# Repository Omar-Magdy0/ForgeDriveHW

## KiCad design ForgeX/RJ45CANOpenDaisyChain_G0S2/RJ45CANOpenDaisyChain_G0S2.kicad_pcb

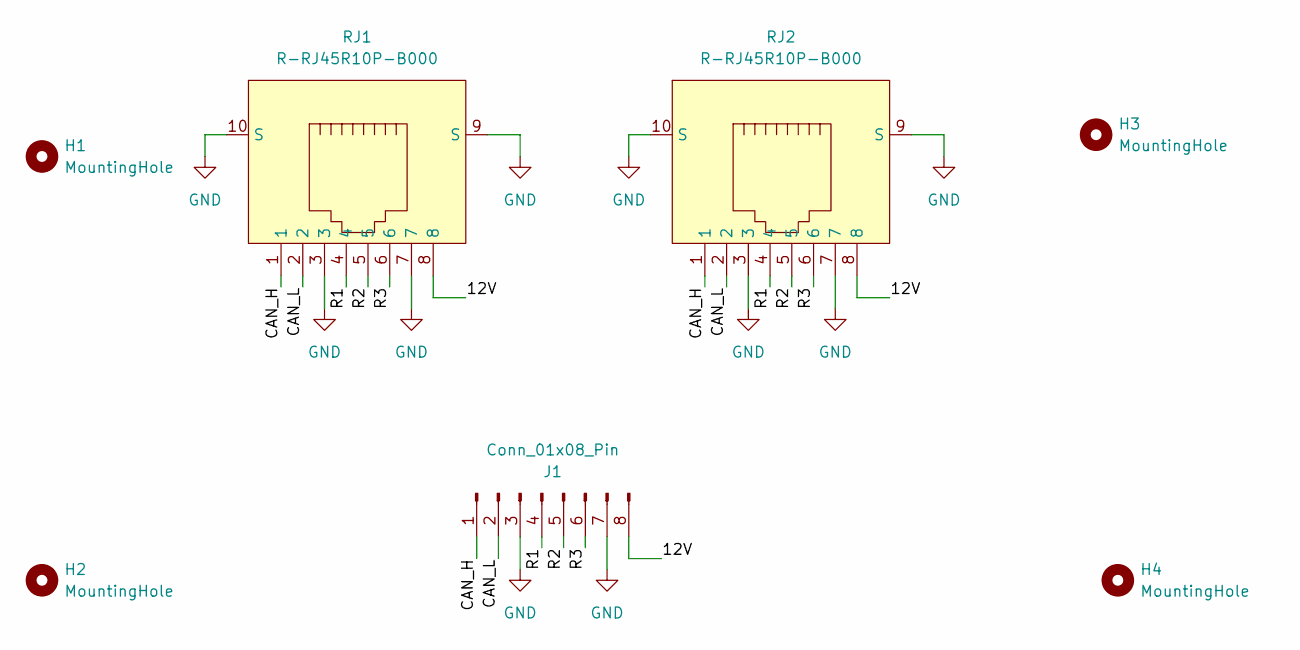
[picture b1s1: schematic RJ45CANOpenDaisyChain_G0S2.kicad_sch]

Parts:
H1, H2, H3, H4: MountingHole; MountingHole_3.2mm_M3_DIN965_Pad_TopBottom
J1: Conn_01x08_Pin; P2.54_WirePad_Header
RJ1, RJ2: R-RJ45R10P-B000; RJ45-TH_R-RJ45R10P-B000; MPN R-RJ45R10P-B000; LCSC Part C386758

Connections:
/12V: J1.8, RJ1.8, RJ2.8
/CAN_H: J1.1, RJ1.1, RJ2.1
/CAN_L: J1.2, RJ1.2, RJ2.2
/R1: J1.4, RJ1.4, RJ2.4
/R2: J1.5, RJ1.5, RJ2.5
/R3: J1.6, RJ1.6, RJ2.6
GND: J1.3, J1.7, RJ1.3, RJ1.7, RJ1.9 (S), RJ1.10 (S), RJ2.3, RJ2.7, RJ2.9 (S), RJ2.10 (S)

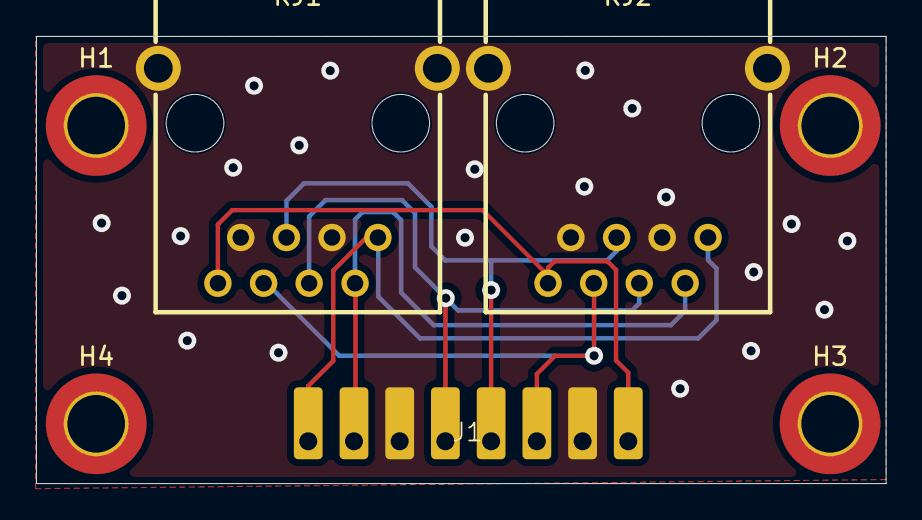
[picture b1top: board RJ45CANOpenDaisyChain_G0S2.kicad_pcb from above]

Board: 2 copper layers, 47.2 x 24.8 mm, 7 parts (0 on the bottom side), 7 nets.

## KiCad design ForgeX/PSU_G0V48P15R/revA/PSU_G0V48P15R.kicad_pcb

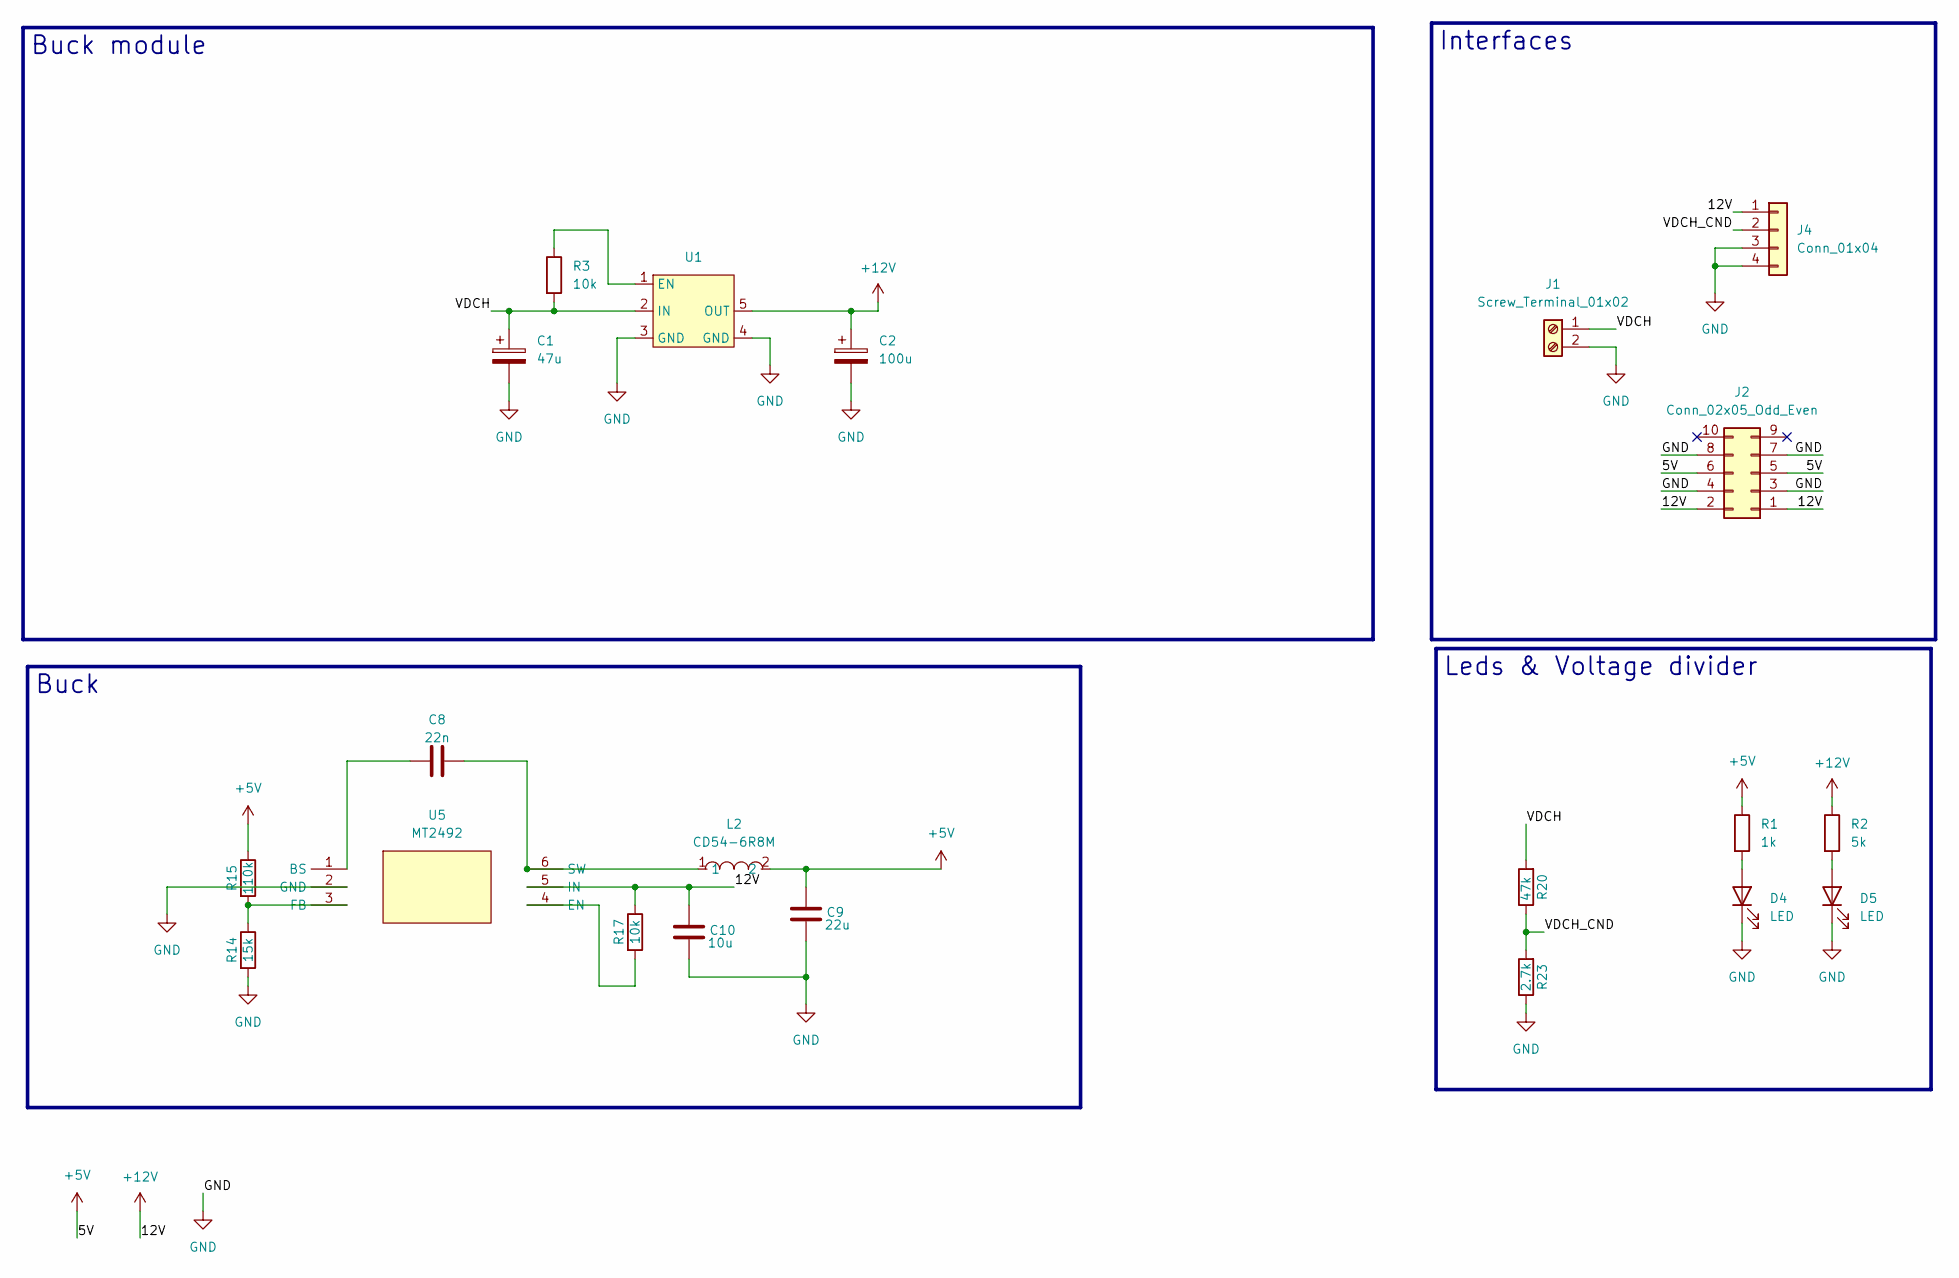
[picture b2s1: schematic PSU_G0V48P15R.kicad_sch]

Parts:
C1: 47u; CP_Radial_D10.0mm_P3.50mm
C2: 100u; CP_Radial_D10.0mm_P3.50mm
C8: 22n; C_0603_1608Metric_Pad1.08x0.95mm_HandSolder
C9: 22u; C_1206_3216Metric_Pad1.33x1.80mm_HandSolder
C10: 10u; C_1206_3216Metric_Pad1.33x1.80mm_HandSolder
D4, D5: LED; LED_1206_3216Metric_Pad1.42x1.75mm_HandSolder
J1: Screw_Terminal_01x02; SPACER_M3_PCONN_PSU
J2: Conn_02x05_Odd_Even; PinHeader_2x05_P2.54mm_Vertical
J4: Conn_01x04; JST_XH_B4B-XH-A_1x04_P2.50mm_Vertical
L2: CD54-6R8M; IND-SMD_L5.8-W5.2_CD54; MPN CD54-6R8M; LCSC Part C7588992
R1: 1k; R_1206_3216Metric_Pad1.30x1.75mm_HandSolder
R2: 5k; R_1206_3216Metric_Pad1.30x1.75mm_HandSolder
R3: 10k; R_1206_3216Metric_Pad1.30x1.75mm_HandSolder
R14: 15k; R_0603_1608Metric_Pad0.98x0.95mm_HandSolder
R15: 110k; R_0603_1608Metric_Pad0.98x0.95mm_HandSolder
R17: 10k; R_0603_1608Metric_Pad0.98x0.95mm_HandSolder
R20: 47k; R_1206_3216Metric_Pad1.30x1.75mm_HandSolder
R23: 2.7k; R_1206_3216Metric_Pad1.30x1.75mm_HandSolder
U1: HW-788abcd
U5: MT2492; SOT-23-6_L2.9-W1.6-P0.95-LS2.8-BL_3; MPN MT2492; LCSC Part C89358

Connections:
+5V: C9.1, J2.5, J2.6, L2.2, R1.1, R15.1
+12V: C2.1, C10.1, J2.1, J2.2, J4.1, R2.1, R17.1, U1.5 (OUT), U5.5 (IN)
/VDCH: C1.1, J1.1, R3.2, R20.2, U1.2 (IN)
/VDCH_CND: J4.2, R20.1, R23.2
GND: C1.2, C2.2, C9.2, C10.2, D4.1 (K), D5.1 (K), J1.2, J2.3, J2.4, J2.7, J2.8, J4.3, J4.4, R14.2, R23.1, U1.3 (GND), U1.4 (GND), U5.2 (GND)
unnamed: D4.2 (A), R1.2
unnamed: D5.2 (A), R2.2
unnamed: R3.1, U1.1 (EN)
unnamed: C8.2, U5.1 (BS)
unnamed: R17.2, U5.4 (EN)
unnamed: R14.1, R15.2, U5.3 (FB)
unnamed: C8.1, L2.1, U5.6 (SW)

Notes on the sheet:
Buck module
Buck
Interfaces
Leds & Voltage divider

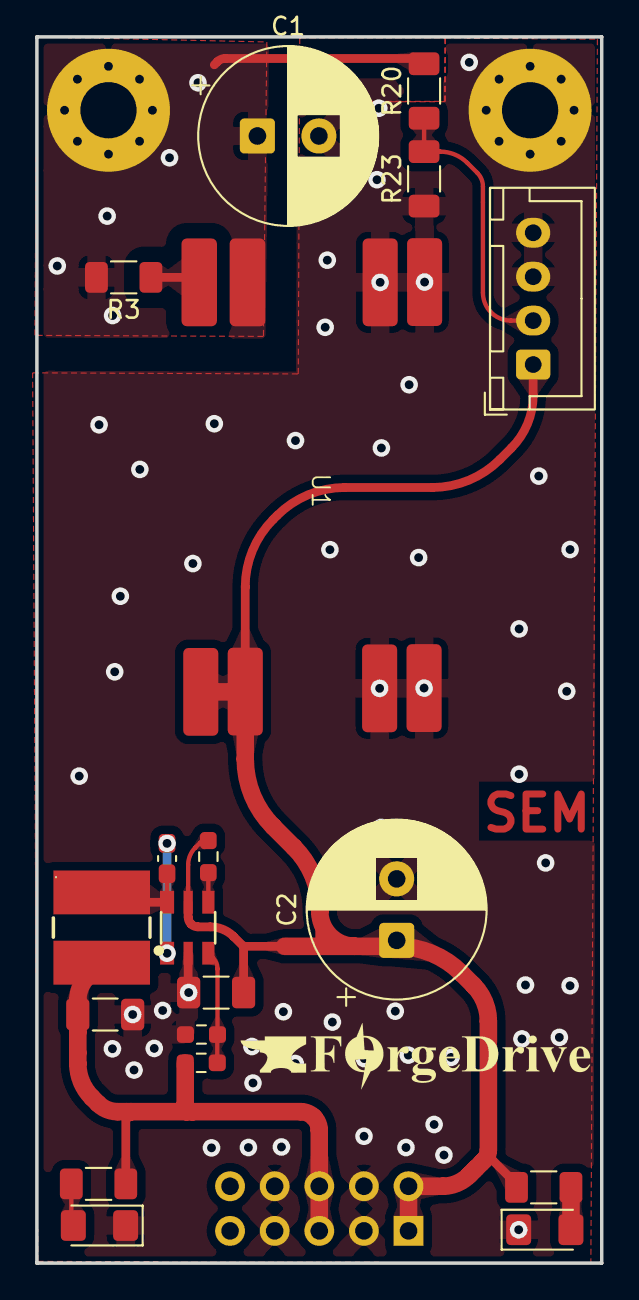
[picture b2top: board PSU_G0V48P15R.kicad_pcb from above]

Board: 2 copper layers, 32.1 x 69.8 mm, 21 parts (1 on the bottom side), 12 nets.

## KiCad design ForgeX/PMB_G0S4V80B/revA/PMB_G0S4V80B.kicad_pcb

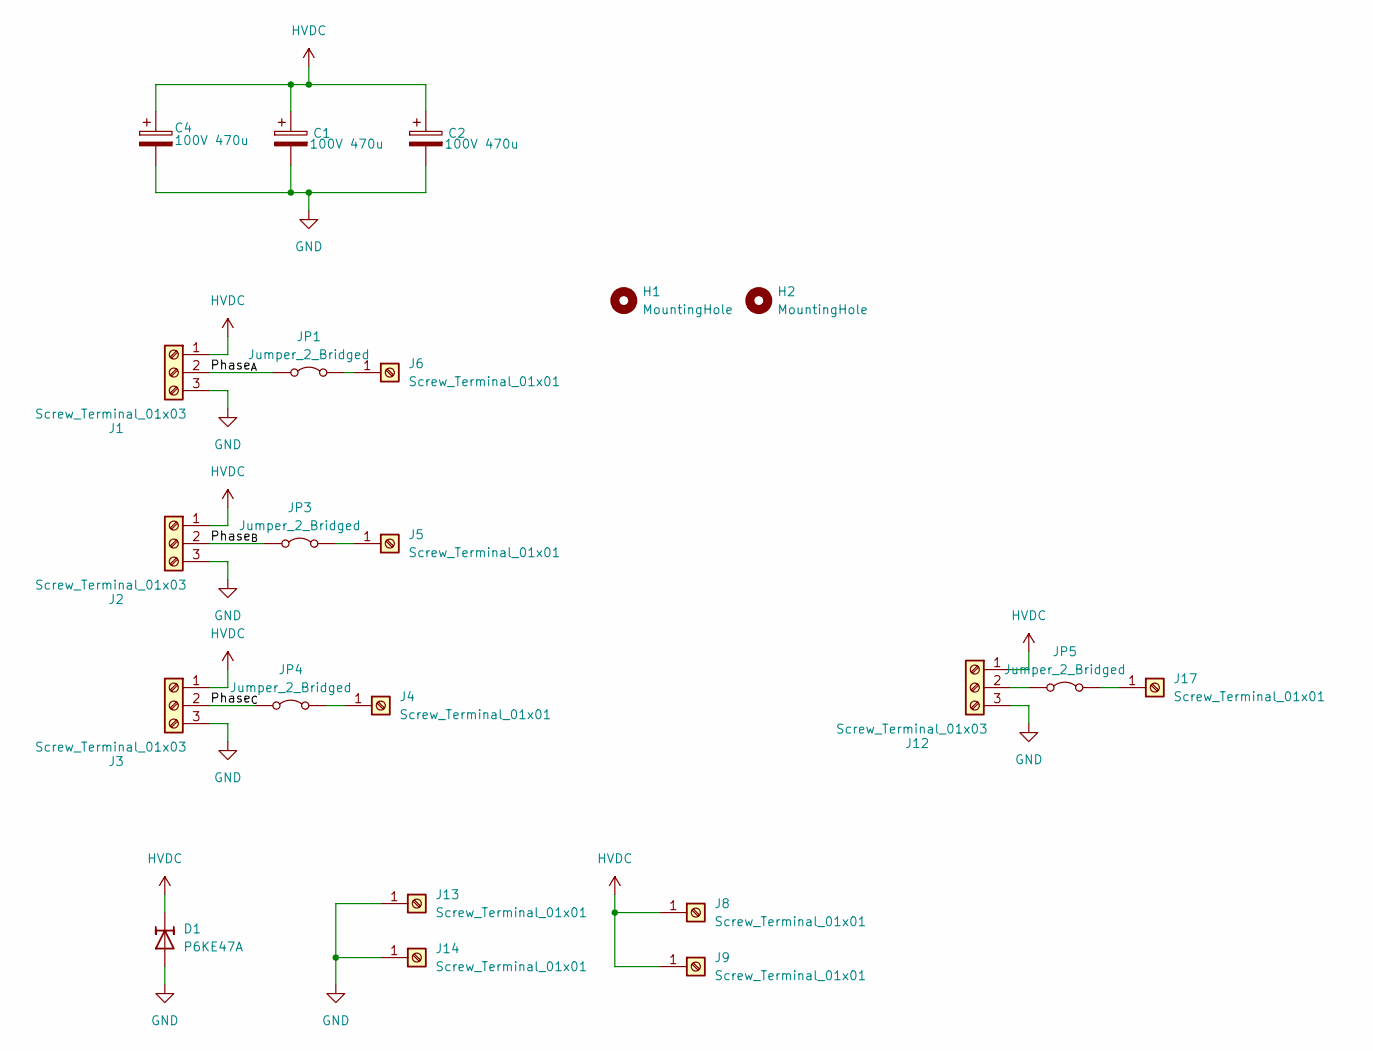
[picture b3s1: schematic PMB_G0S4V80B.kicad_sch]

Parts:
C1, C2, C4: 100V 470u; CP_Radial_D18.0mm_P7.50mm
D1: P6KE47A; D_DO-15_P10.16mm_Horizontal
H1, H2: MountingHole; MountingHole_5.3mm_M5_DIN965
J1, J2, J3, J12: Screw_Terminal_01x03; SPACER_M3_PCONN_2x03
J4, J5, J6, J8, J9, J13, J14, J17: Screw_Terminal_01x01; M3_PCONN_1x01
JP1, JP3, JP4, JP5: Jumper_2_Bridged; PowerJumper_PMB

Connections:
/Phase_{A}: J1.2, JP1.1 (A)
/Phase_{B}: J2.2, JP3.1 (A)
/Phase_{C}: J3.2, JP4.1 (A)
GND: C1.2, C2.2, C4.2, D1.2 (A), J1.3, J2.3, J3.3, J12.3, J13.1 (Pin_1_1), J14.1 (Pin_1_1)
HVDC: C1.1, C2.1, C4.1, D1.1 (K), J1.1, J2.1, J3.1, J8.1 (Pin_1_1), J9.1 (Pin_1_1), J12.1
unnamed: J4.1 (Pin_1_1), JP4.2 (B)
unnamed: J5.1 (Pin_1_1), JP3.2 (B)
unnamed: J6.1 (Pin_1_1), JP1.2 (B)
unnamed: J12.2, JP5.1 (A)
unnamed: J17.1 (Pin_1_1), JP5.2 (B)

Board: 2 copper layers, 22 parts (0 on the bottom side), 10 nets, no tracks yet.

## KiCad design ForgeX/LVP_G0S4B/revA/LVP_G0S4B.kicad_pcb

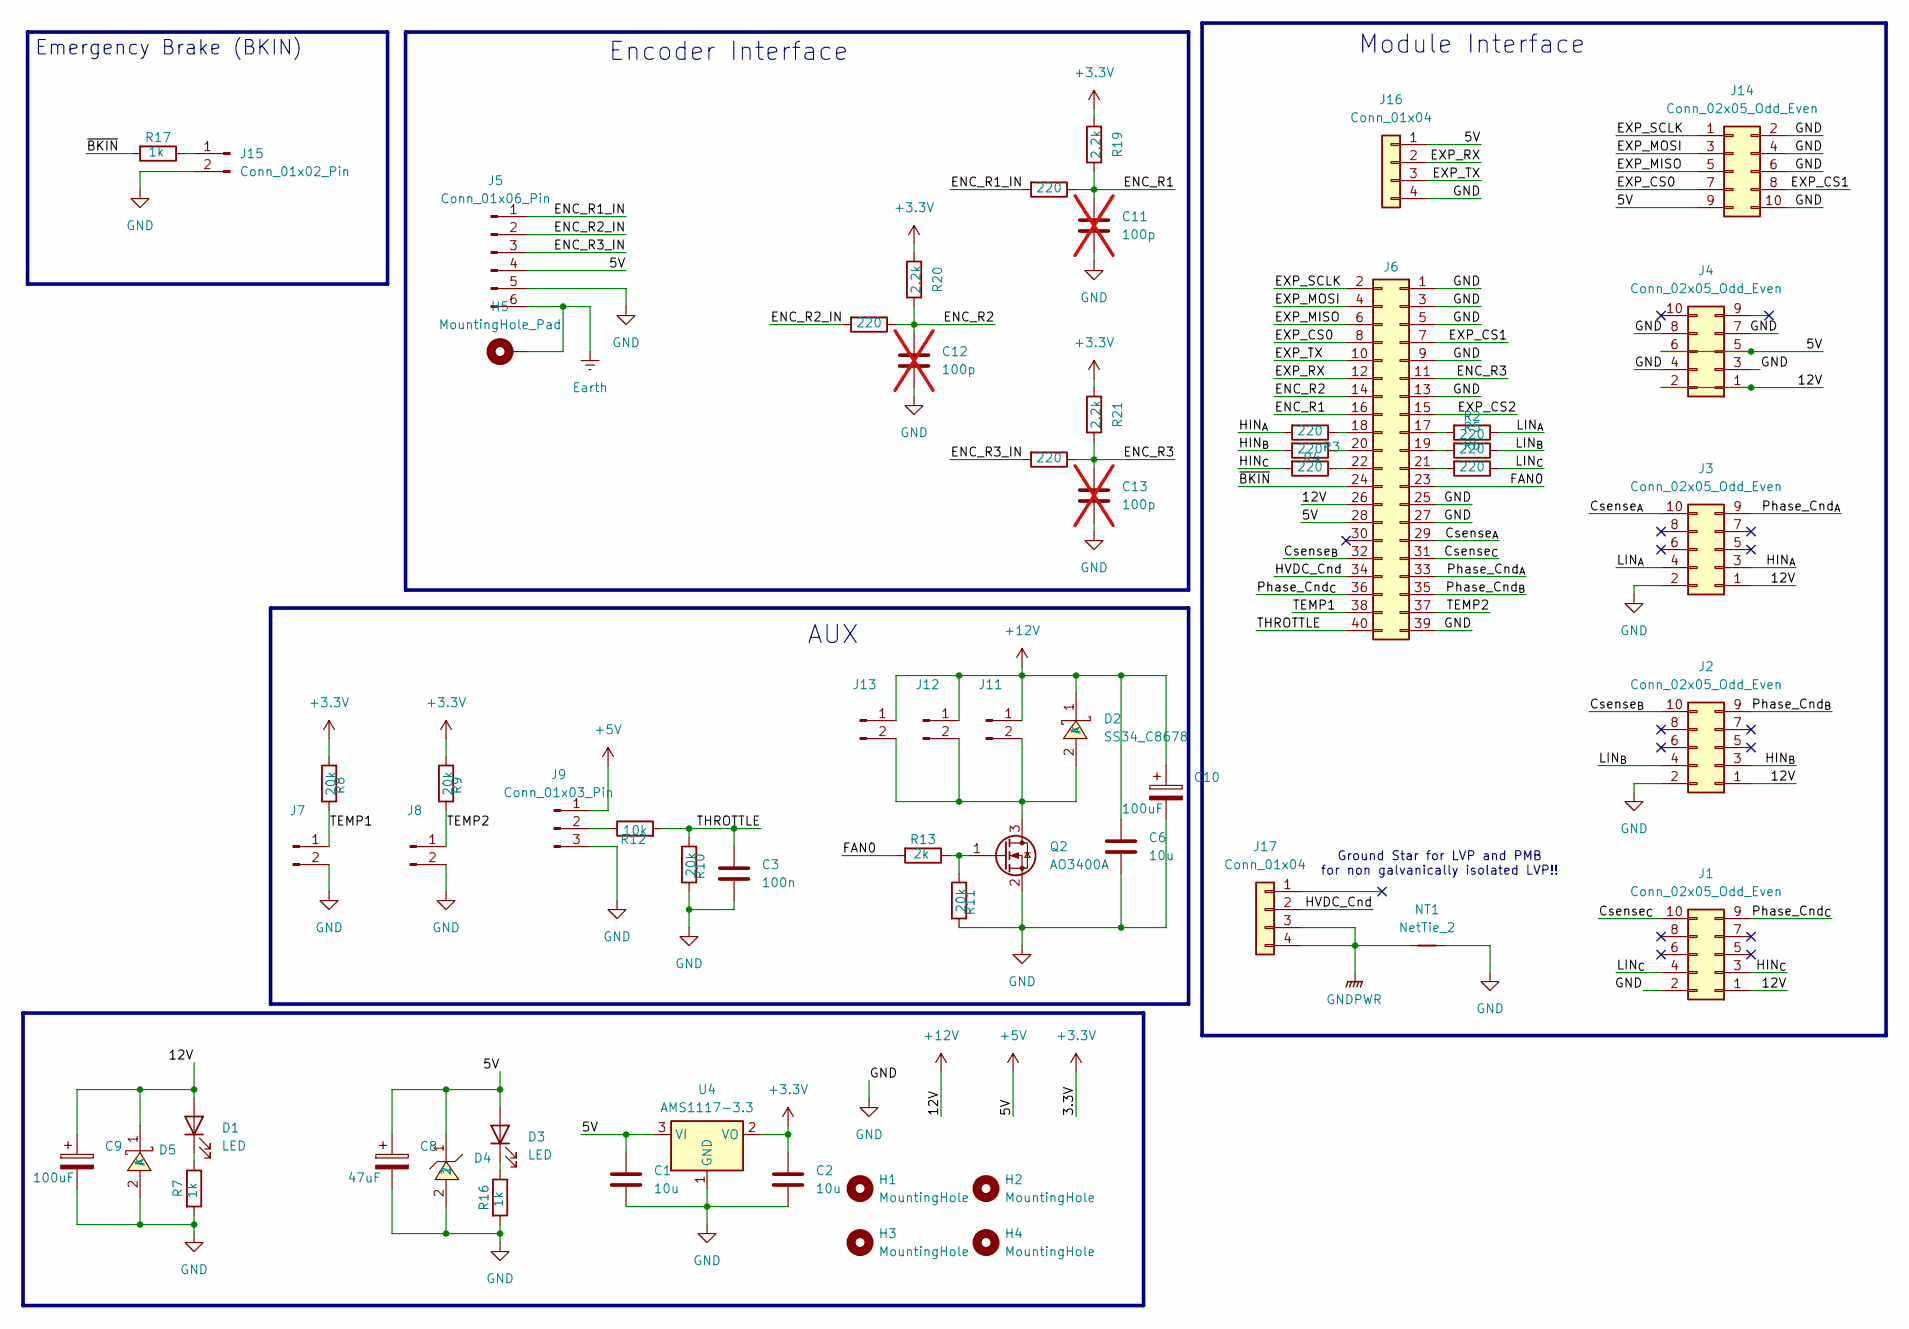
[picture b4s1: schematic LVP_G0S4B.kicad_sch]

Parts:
C1, C2, C6: 10u; C_1206_3216Metric_Pad1.33x1.80mm_HandSolder
C3: 100n; C_0603_1608Metric_Pad1.08x0.95mm_HandSolder
C8: 47uF; CP_Elec_5x5.4
C9, C10: 100uF; CP_Elec_8x6.5
C11, C12, C13: 100p; C_0603_1608Metric_Pad1.08x0.95mm_HandSolder; not fitted
D1, D3: LED; LED_0603_1608Metric
D2: SS34_C8678; SMA_L4.3-W2.6-LS5.2-RD; MPN SS34; LCSC Part C8678
D4: SMBJ5.0A_C83333; SMB_L4.6-W3.6-LS5.3-RD; MPN SMBJ5.0A; LCSC Part C83333
D5: SMBJ12A_C151251; SMB_L4.6-W3.6-LS5.3-RD; MPN SMBJ12A; LCSC Part C151251
H1, H2, H3, H4: MountingHole; MountingHole_3.2mm_M3_DIN965
H5: MountingHole_Pad; MountingHole_3.2mm_M3_Pad_Via
J1, J2, J3, J4: Conn_02x05_Odd_Even; PinSocket_2x05_P2.54mm_Vertical
J5: Conn_01x06_Pin; JST_XH_B6B-XH-A_1x06_P2.50mm_Vertical
J6: Conn_02x20_Odd_Even; PinSocket_2x20_P2.54mm_Vertical
J7, J8, J11, J12, J13, J15: Conn_01x02_Pin; JST_XH_B2B-XH-A_1x02_P2.50mm_Vertical
J9: Conn_01x03_Pin; JST_XH_B3B-XH-A_1x03_P2.50mm_Vertical
J14: Conn_02x05_Odd_Even; IDC-Header_2x05_P2.54mm_Vertical
J16: Conn_01x04; PinSocket_1x04_P2.54mm_Vertical
J17: Conn_01x04; JST_XH_B4B-XH-A_1x04_P2.50mm_Vertical
NT1: NetTie_2; ground_tie
Q2: AO3400A; SOT-23
R1, R2, R3, R4, R5, R6, R14, R15, R18: 220; R_0603_1608Metric_Pad0.98x0.95mm_HandSolder
R7, R16, R17: 1k; R_0603_1608Metric_Pad0.98x0.95mm_HandSolder
R8, R9, R11: 20k; R_1206_3216Metric_Pad1.30x1.75mm_HandSolder
R10: 20k; R_0603_1608Metric_Pad0.98x0.95mm_HandSolder
R12: 10k; R_0603_1608Metric_Pad0.98x0.95mm_HandSolder
R13: 2k; R_1206_3216Metric_Pad1.30x1.75mm_HandSolder
R19, R20, R21: 2.2k; R_0603_1608Metric_Pad0.98x0.95mm_HandSolder
U4: AMS1117-3.3; SOT-89-3

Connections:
+3.3V: C2.1, R8.2, R9.2, R19.2, R20.2, R21.2, U4.2 (VO)
+5V: C1.1, C8.1, D3.2 (A), D4.1, J4.5, J4.6, J5.4, J6.28, J9.1, J14.9, J16.1, U4.3 (VI)
+12V: C6.1, C9.1, C10.1, D1.2 (A), D2.1 (K), D5.1 (K), J1.1, J2.1, J3.1, J4.1, J4.2, J6.26, J11.1, J12.1, J13.1
/Csense_{A}: J3.10, J6.29
/Csense_{B}: J2.10, J6.32
/Csense_{C}: J1.10, J6.31
/ENC_R1: C11.1, J6.16, R14.1, R19.1
/ENC_R1_IN: J5.1, R14.2
/ENC_R2: C12.1, J6.14, R15.1, R20.1
/ENC_R2_IN: J5.2, R15.2
/ENC_R3: C13.1, J6.11, R18.1, R21.1
/ENC_R3_IN: J5.3, R18.2
/EXP_CS0: J6.8, J14.7
/EXP_CS1: J6.7, J14.8
/EXP_CS2: J6.15
/EXP_MISO: J6.6, J14.5
/EXP_MOSI: J6.4, J14.3
/EXP_RX: J6.12, J16.2
/EXP_SCLK: J6.2, J14.1
/EXP_TX: J6.10, J16.3
/FAN0: J6.23, R13.2
/HIN_{A}: J3.3, R1.2
/HIN_{B}: J2.3, R3.2
/HIN_{C}: J1.3, R4.2
/HVDC_Cnd: J6.34, J17.2
/LIN_{A}: J3.4, R2.1
/LIN_{B}: J2.4, R5.1
/LIN_{C}: J1.4, R6.1
/Phase_Cnd_{A}: J3.9, J6.33
/Phase_Cnd_{B}: J2.9, J6.35
/Phase_Cnd_{C}: J1.9, J6.36
/TEMP1: J6.38, J7.1, R8.1
/TEMP2: J6.37, J8.1, R9.1
/THROTTLE: C3.1, J6.40, R10.2, R12.2
/~BKIN: J6.24, R17.2
Earth: H5.1 (1_1), J5.6
GND: C1.2, C2.2, C3.2, C6.2, C8.2, C9.2, C10.2, C11.2, C12.2, C13.2, D4.2, D5.2 (A), J1.2, J2.2, J3.2, J4.3, J4.4, J4.7, J4.8, J5.5, J6.1, J6.3, J6.5, J6.9, J6.13, J6.25, J6.27, J6.39, J7.2, J8.2, J9.3, J14.2, J14.4, J14.6, J14.10, J15.2, J16.4, NT1.2, Q2.2 (S), R7.2, R10.1, R11.1, R16.2, U4.1 (GND)
GNDPWR: J17.3, J17.4, NT1.1
unnamed: D1.1 (K), R7.1
unnamed: D2.2 (A), J11.2, J12.2, J13.2, Q2.3 (D)
unnamed: D3.1 (K), R16.1
unnamed: J6.17, R2.2
unnamed: J6.18, R1.1
unnamed: J6.19, R5.2
unnamed: J6.20, R3.1
unnamed: J6.21, R6.2
unnamed: J6.22, R4.1
unnamed: J9.2, R12.1
unnamed: J15.1, R17.1
unnamed: Q2.1 (G), R11.2, R13.1

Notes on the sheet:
Ground Star for LVP and PMB for non galvanically isolated LVP!!
AUX
Encoder Interface
Module Interface
Emergency Brake (BKIN)

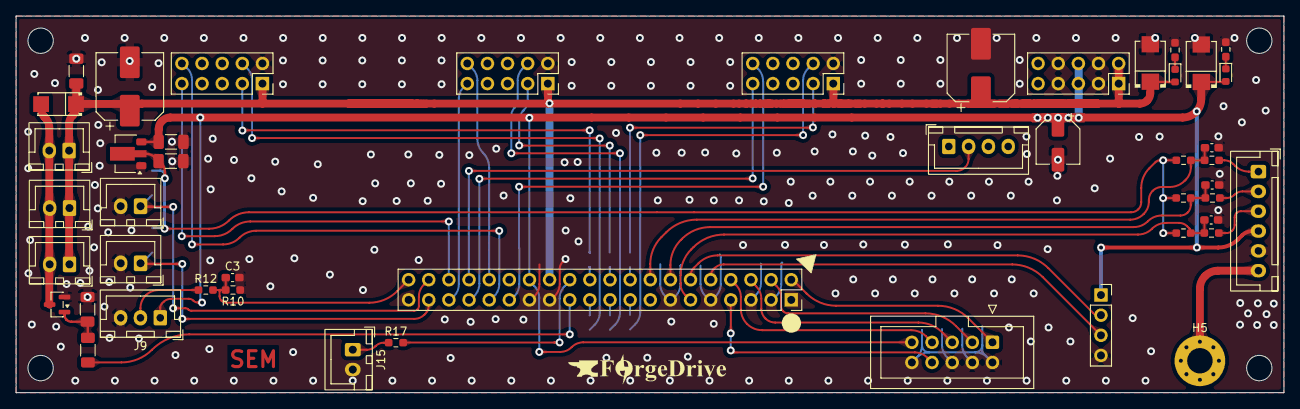
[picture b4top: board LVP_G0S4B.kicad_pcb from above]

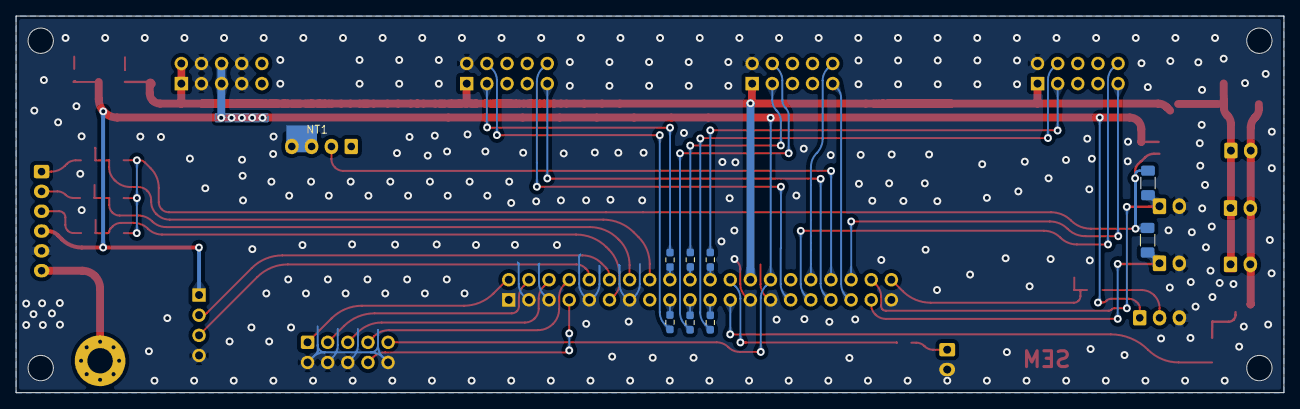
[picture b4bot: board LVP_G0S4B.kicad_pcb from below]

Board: 2 copper layers, 159.9 x 47.5 mm, 60 parts (9 on the bottom side), 49 nets.

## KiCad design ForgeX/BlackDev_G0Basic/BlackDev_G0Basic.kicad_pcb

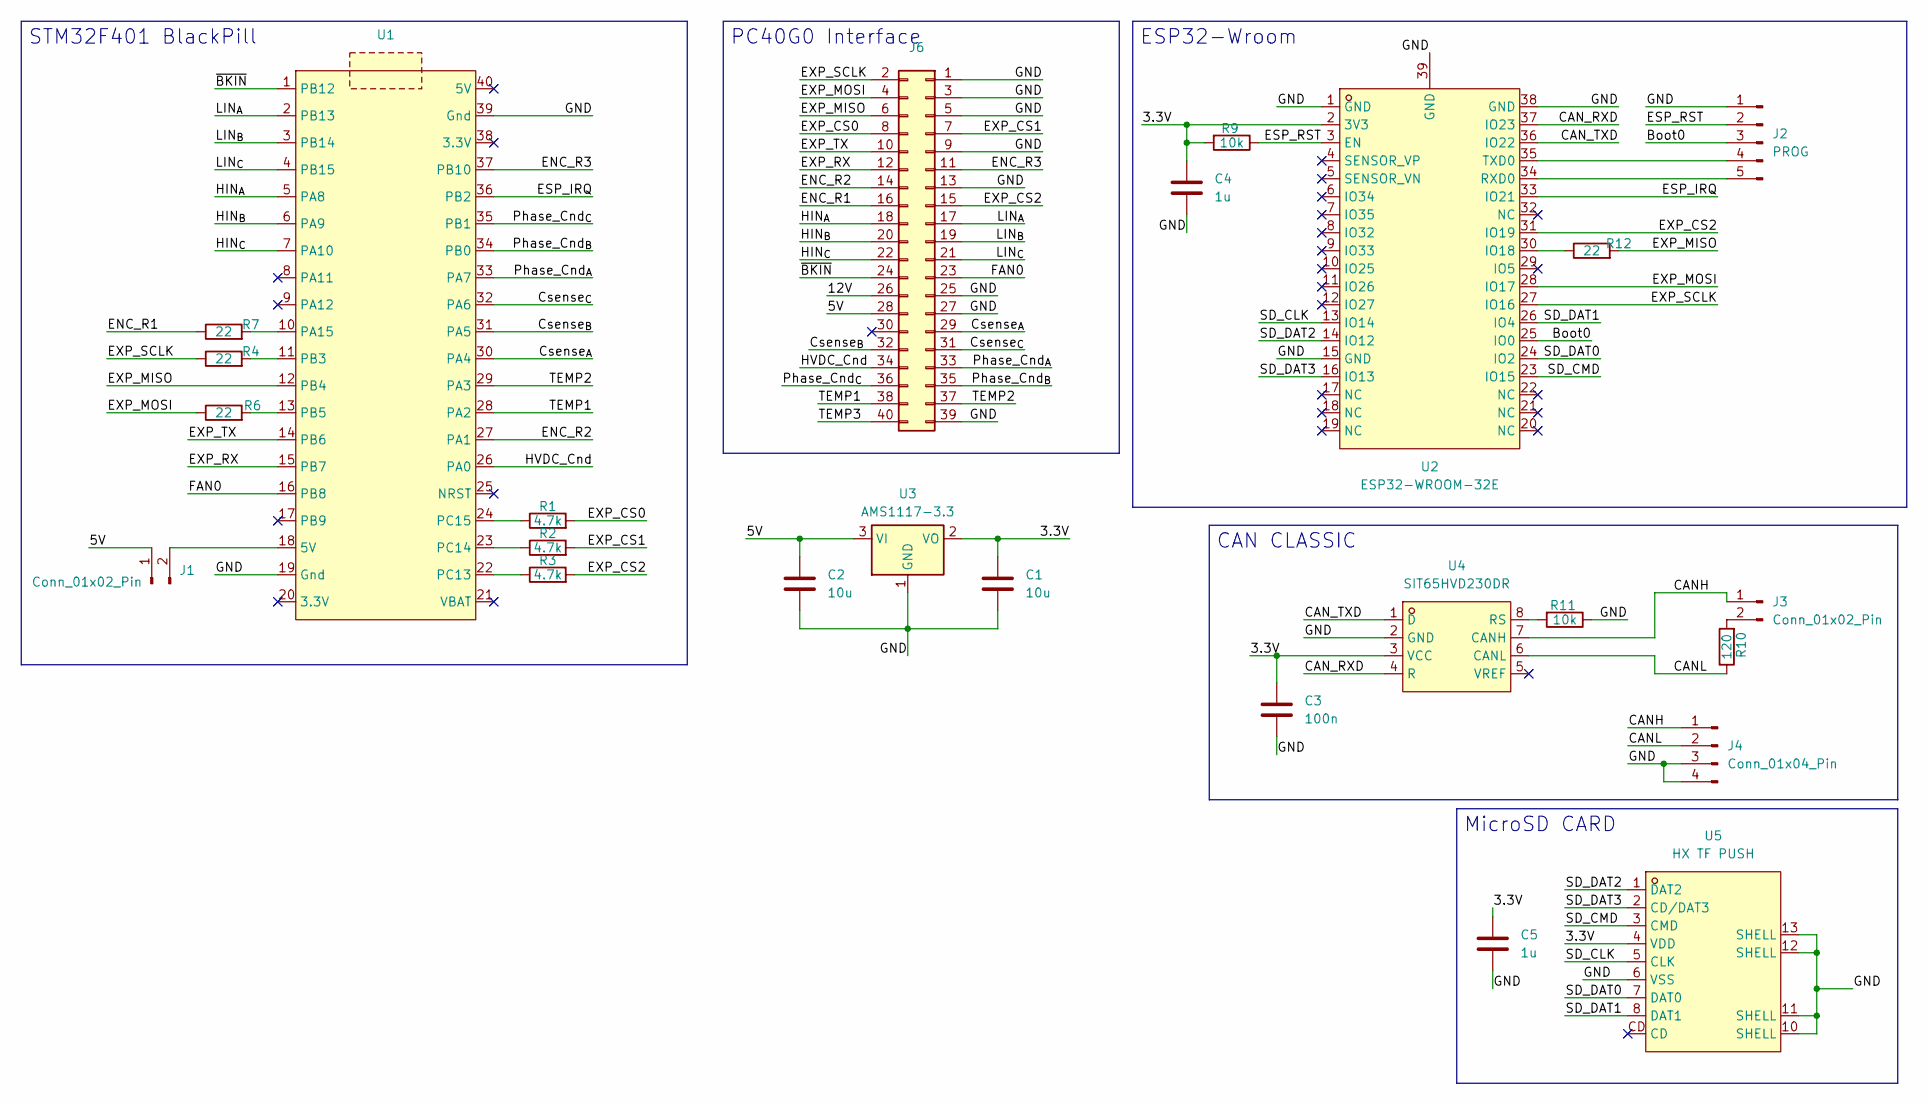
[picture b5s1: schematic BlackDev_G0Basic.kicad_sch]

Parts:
C1, C2: 10u; C_1206_3216Metric_Pad1.33x1.80mm_HandSolder
C3: 100n; C_0603_1608Metric_Pad1.08x0.95mm_HandSolder
C4, C5: 1u; C_0603_1608Metric_Pad1.08x0.95mm_HandSolder
J1: Conn_01x02_Pin; PinHeader_1x02_P2.54mm_Vertical_SMD_Pin1Right
J2: PROG; PinHeader_1x05_P2.54mm_Vertical_SMD_Pin1Left
J3: Conn_01x02_Pin; PinHeader_1x02_P2.54mm_Vertical
J4: Conn_01x04_Pin; JST_XH_B4B-XH-A_1x04_P2.50mm_Vertical
J6: Conn_02x20_Odd_Even; PinHeader_2x20_P2.54mm_Vertical
R1, R2, R3: 4.7k; R_0603_1608Metric_Pad0.98x0.95mm_HandSolder
R4, R6, R7, R12: 22; R_0603_1608Metric_Pad0.98x0.95mm_HandSolder
R9, R11: 10k; C_0603_1608Metric_Pad1.08x0.95mm_HandSolder
R10: 120; R_1206_3216Metric_Pad1.30x1.75mm_HandSolder
U1: Stm32BlackPill
U2: ESP32-WROOM-32E; WIFI-SMD_ESP32-WROOM-32E; MPN ESP32-WROOM-32E-N4; LCSC Part C701341
U3: AMS1117-3.3; SOT-223-3_TabPin2
U4: SIT65HVD230DR; SOP-8_L4.9-W3.9-P1.27-LS6.0-BL; MPN SIT65HVD230DR; LCSC Part C496619
U5: HX TF PUSH; TF-SMD_TF-PUSH; MPN HX TF PUSH; LCSC Part C5184837

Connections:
/3.3V: C1.1, C3.1, C4.1, C5.1, R9.2, U2.2 (3V3), U3.2 (VO), U4.3 (VCC), U5.4 (VDD)
/5V: C2.1, J1.1, J6.28, U3.3 (VI)
/12V: J6.26
/Boot0: J2.3, U2.25 (IO0)
/CANH: J3.1, J4.1, U4.7 (CANH)
/CANL: J4.2, R10.1, U4.6 (CANL)
/CAN_RXD: U2.37 (IO23), U4.4 (R)
/CAN_TXD: U2.36 (IO22), U4.1 (D)
/Csense_{A}: J6.29, U1.30 (PA4)
/Csense_{B}: J6.32, U1.31 (PA5)
/Csense_{C}: J6.31, U1.32 (PA6)
/ENC_R1: J6.16, R7.1
/ENC_R2: J6.14, U1.27 (PA1)
/ENC_R3: J6.11, U1.37 (PB10)
/ESP_IRQ: U1.36 (PB2), U2.33 (IO21)
/ESP_RST: J2.2, R9.1, U2.3 (EN)
/EXP_CS0: J6.8, R1.2
/EXP_CS1: J6.7, R2.2
/EXP_CS2: J6.15, R3.2, U2.31 (IO19)
/EXP_MISO: J6.6, R12.2, U1.12 (PB4)
/EXP_MOSI: J6.4, R6.1, U2.28 (IO17)
/EXP_RX: J6.12, U1.15 (PB7)
/EXP_SCLK: J6.2, R4.1, U2.27 (IO16)
/EXP_TX: J6.10, U1.14 (PB6)
/FAN0: J6.23, U1.16 (PB8)
/GND: C1.2, C2.2, C3.2, C4.2, C5.2, J2.1, J4.3, J4.4, J6.1, J6.3, J6.5, J6.9, J6.13, J6.25, J6.27, J6.39, R11.1, U1.19 (Gnd), U1.39 (Gnd), U2.1 (GND), U2.15 (GND), U2.38 (GND), U2.39 (GND), U3.1 (GND), U4.2 (GND), U5.6 (VSS), U5.10 (SHELL), U5.11 (SHELL), U5.12 (SHELL), U5.13 (SHELL)
/HIN_{A}: J6.18, U1.5 (PA8)
/HIN_{B}: J6.20, U1.6 (PA9)
/HIN_{C}: J6.22, U1.7 (PA10)
/HVDC_Cnd: J6.34, U1.26 (PA0)
/LIN_{A}: J6.17, U1.2 (PB13)
/LIN_{B}: J6.19, U1.3 (PB14)
/LIN_{C}: J6.21, U1.4 (PB15)
/Phase_Cnd_{A}: J6.33, U1.33 (PA7)
/Phase_Cnd_{B}: J6.35, U1.34 (PB0)
/Phase_Cnd_{C}: J6.36, U1.35 (PB1)
/SD_CLK: U2.13 (IO14), U5.5 (CLK)
/SD_CMD: U2.23 (IO15), U5.3 (CMD)
/SD_DAT0: U2.24 (IO2), U5.7 (DAT0)
/SD_DAT1: U2.26 (IO4), U5.8 (DAT1)
/SD_DAT2: U2.14 (IO12), U5.1 (DAT2)
/SD_DAT3: U2.16 (IO13), U5.2 (CD/DAT3)
/TEMP1: J6.38, U1.28 (PA2)
/TEMP2: J6.37, U1.29 (PA3)
/TEMP3: J6.40
/~BKIN: J6.24, U1.1 (PB12)
unnamed: J1.2, U1.18 (5V)
unnamed: J2.4, U2.35 (TXD0)
unnamed: J2.5, U2.34 (RXD0)
unnamed: J3.2, R10.2
unnamed: R7.2, U1.10 (PA15)
unnamed: R4.2, U1.11 (PB3)
unnamed: R6.2, U1.13 (PB5)
unnamed: R3.1, U1.22 (PC13)
unnamed: R2.1, U1.23 (PC14)
unnamed: R1.1, U1.24 (PC15)
unnamed: R12.1, U2.30 (IO18)
unnamed: R11.2, U4.8 (RS)

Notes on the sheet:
PC40G0 Interface
STM32F401 BlackPill
ESP32-Wroom
MicroSD CARD
CAN CLASSIC

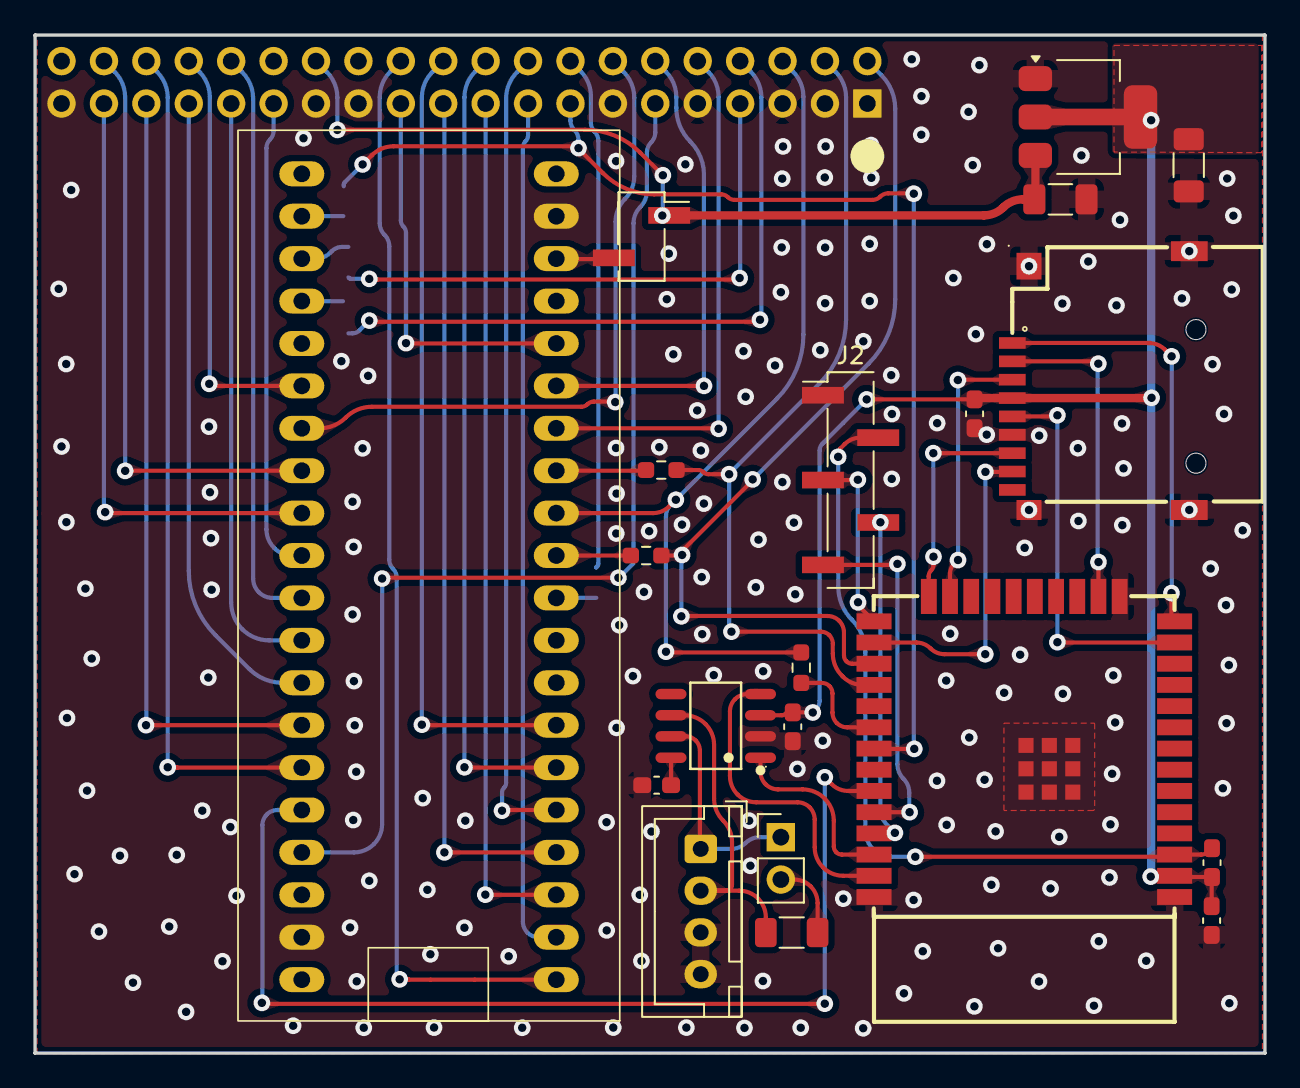
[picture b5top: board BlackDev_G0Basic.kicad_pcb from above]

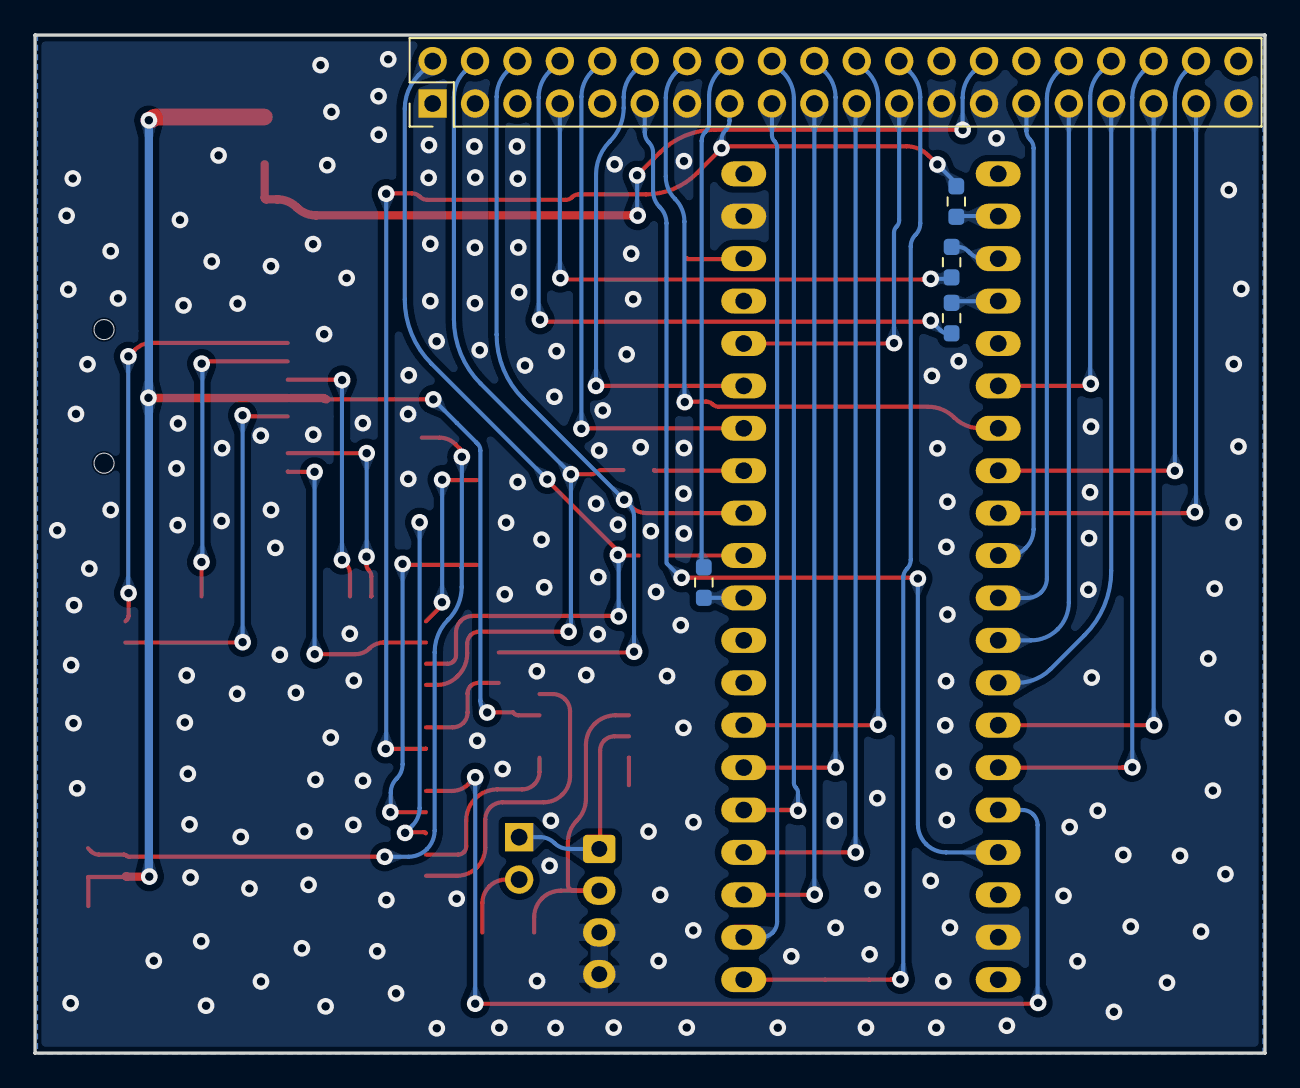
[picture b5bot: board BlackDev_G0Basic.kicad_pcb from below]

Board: 2 copper layers, 73.7 x 61.0 mm, 25 parts (5 on the bottom side), 56 nets.
